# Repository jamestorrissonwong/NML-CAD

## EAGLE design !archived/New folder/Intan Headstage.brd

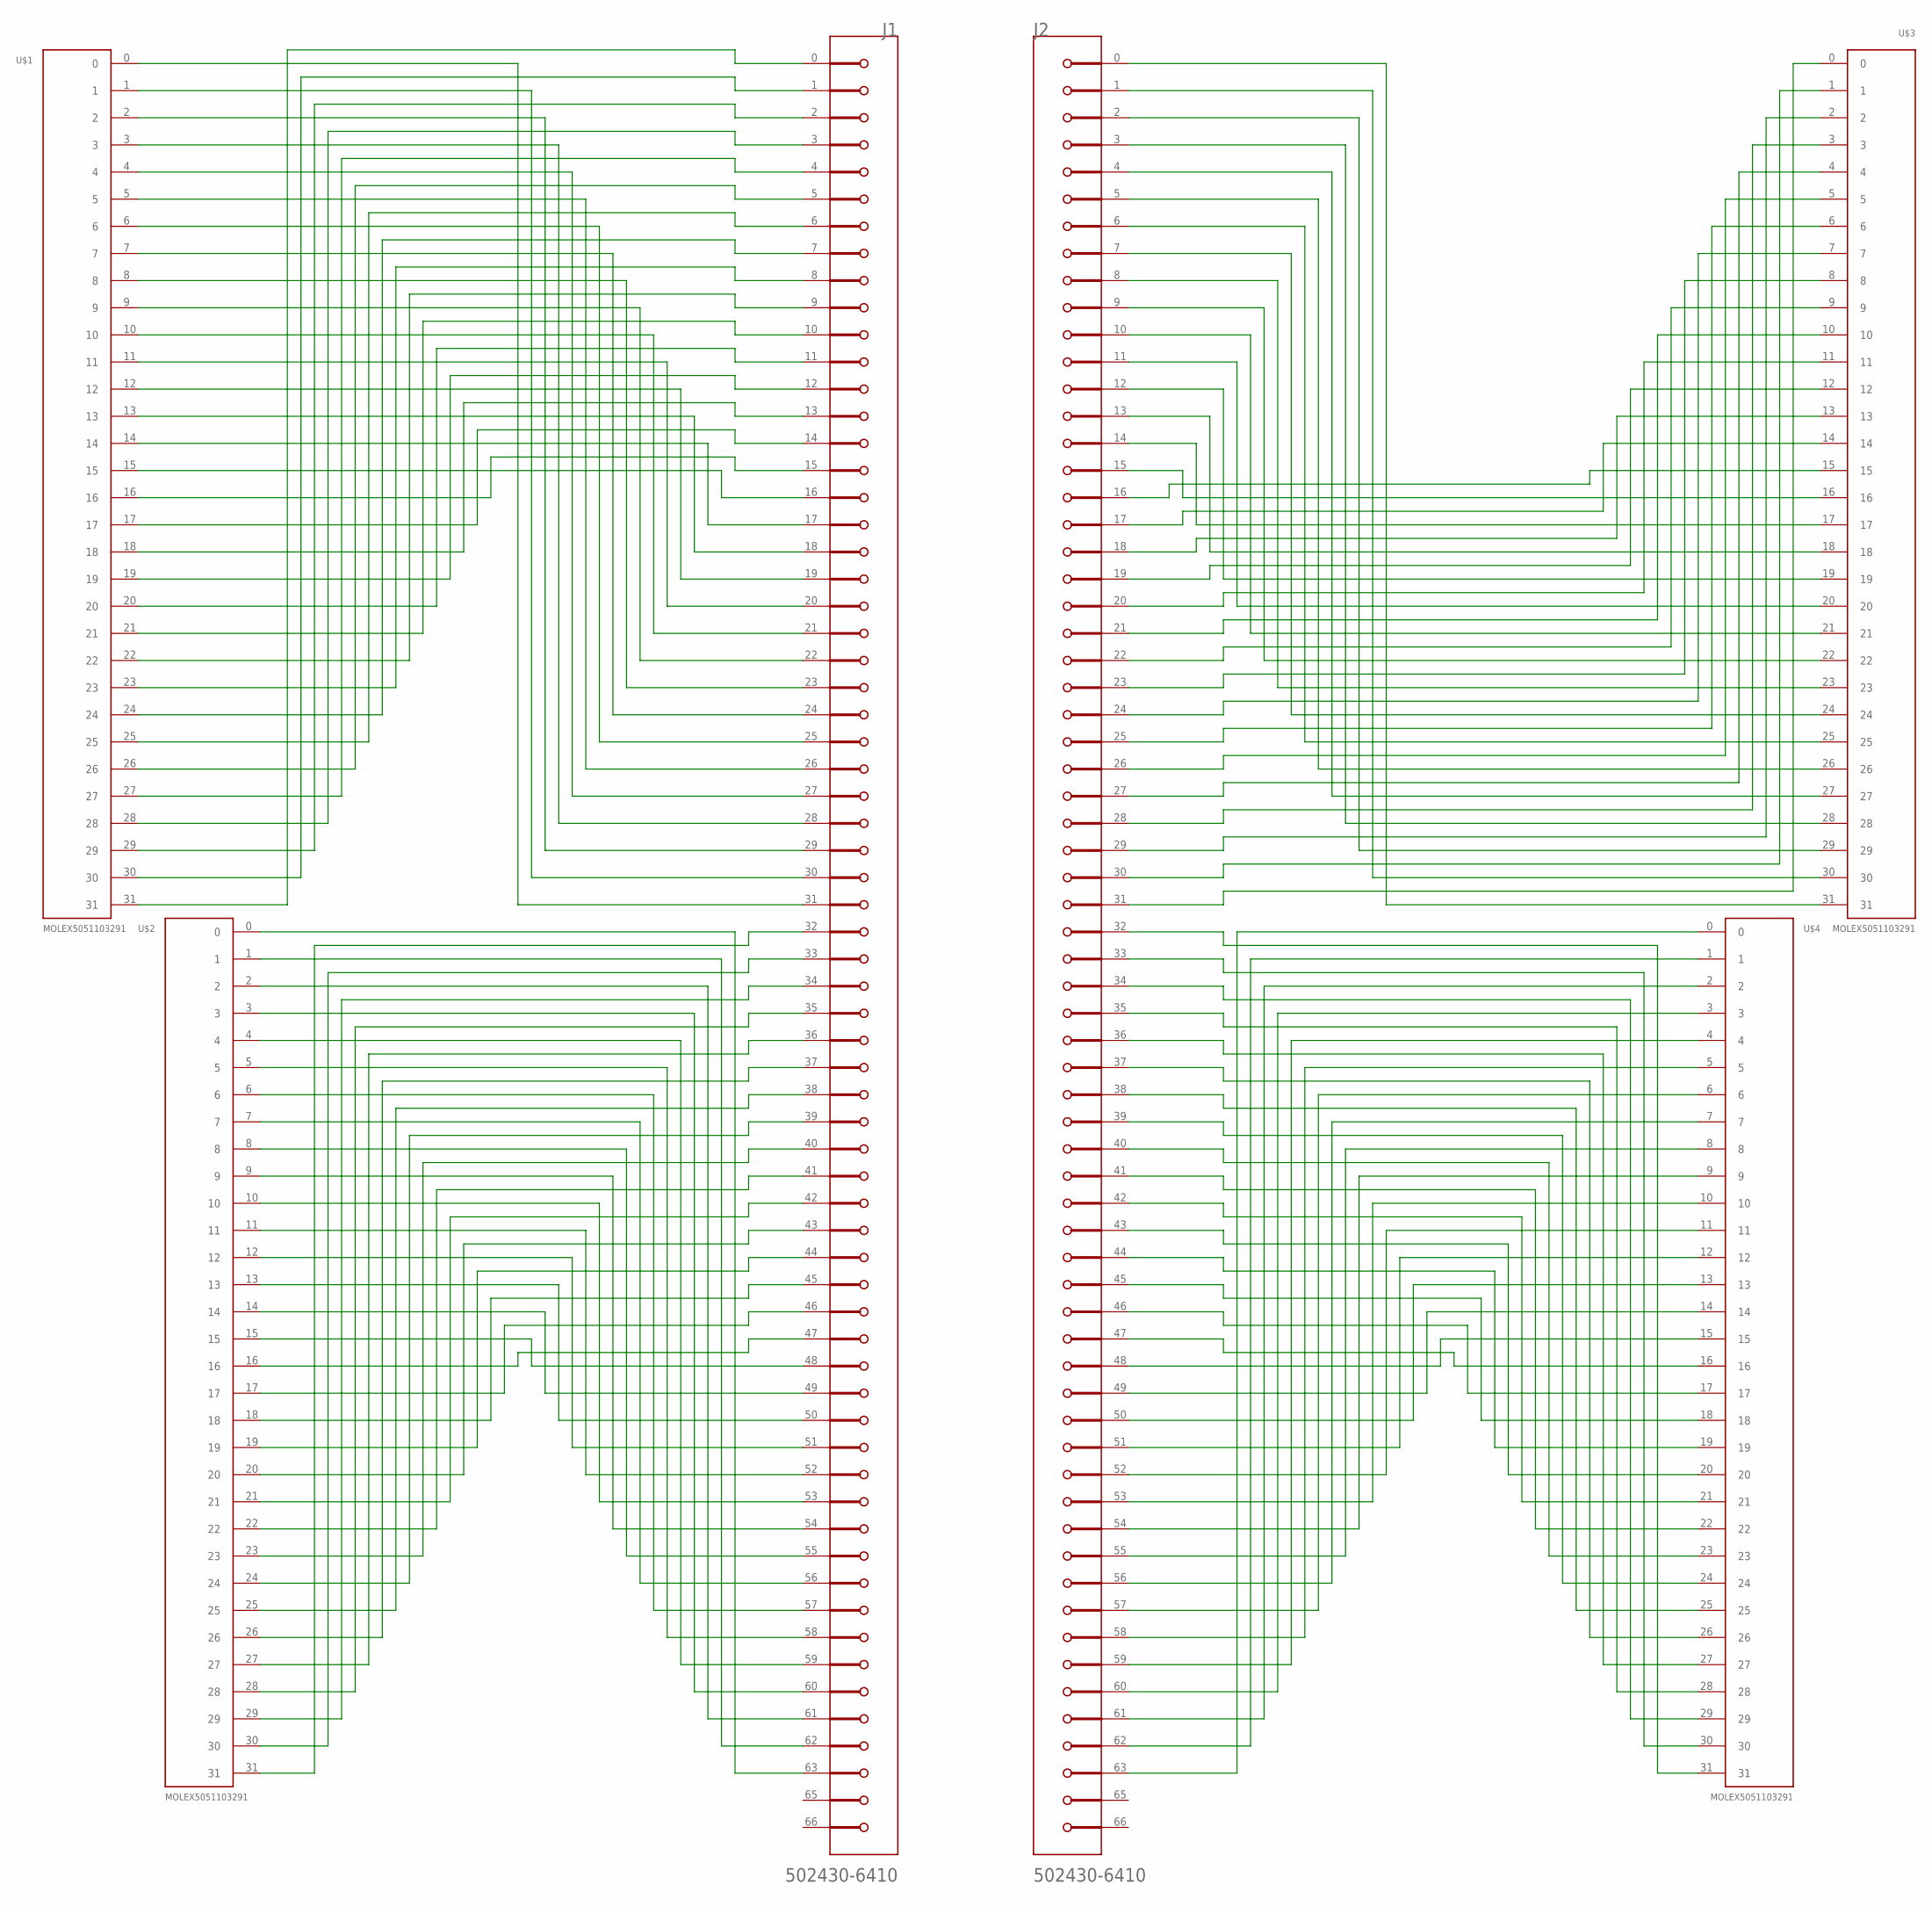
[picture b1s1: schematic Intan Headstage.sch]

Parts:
J1, J2: MOLEX_502430-6410MOLEX_502430-6410_0_0; MOLEX_502430-6410_0
U$1, U$2, U$3, U$4: MOLEX5051103291

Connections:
unnamed: J1.31 (32), U$1.0
unnamed: J1.30 (31), U$1.1
unnamed: J1.29 (30), U$1.2
unnamed: J1.28 (29), U$1.3
unnamed: J1.27 (28), U$1.4
unnamed: J1.26 (27), U$1.5
unnamed: J1.25 (26), U$1.6
unnamed: J1.24 (25), U$1.7
unnamed: J1.23 (24), U$1.8
unnamed: J1.22 (23), U$1.9
unnamed: J1.21 (22), U$1.10
unnamed: J1.20 (21), U$1.11
unnamed: J1.19 (20), U$1.12
unnamed: J1.18 (19), U$1.13
unnamed: J1.17 (18), U$1.14
unnamed: J1.16 (17), U$1.15
unnamed: J1.15 (16), U$1.16
unnamed: J1.14 (15), U$1.17
unnamed: J1.13 (14), U$1.18
unnamed: J1.12 (13), U$1.19
unnamed: J1.11 (12), U$1.20
unnamed: J1.10 (11), U$1.21
unnamed: J1.9 (10), U$1.22
unnamed: J1.8 (9), U$1.23
unnamed: J1.7 (8), U$1.24
unnamed: J1.6 (7), U$1.25
unnamed: J1.5 (6), U$1.26
unnamed: J1.4 (5), U$1.27
unnamed: J1.3 (4), U$1.28
unnamed: J1.2 (3), U$1.29
unnamed: J1.1 (2), U$1.30
unnamed: J1.0 (1), U$1.31
unnamed: J2.0 (1), U$3.31
unnamed: J2.1 (2), U$3.30
unnamed: J2.2 (3), U$3.29
unnamed: J2.3 (4), U$3.28
unnamed: J2.4 (5), U$3.27
unnamed: J2.5 (6), U$3.26
unnamed: J2.6 (7), U$3.25
unnamed: J2.7 (8), U$3.24
unnamed: J2.8 (9), U$3.23
unnamed: J2.9 (10), U$3.22
unnamed: J2.10 (11), U$3.21
unnamed: J2.11 (12), U$3.20
unnamed: J2.12 (13), U$3.19
unnamed: J2.13 (14), U$3.18
unnamed: J2.14 (15), U$3.17
unnamed: J2.15 (16), U$3.16
unnamed: J2.31 (32), U$3.0
unnamed: J2.30 (31), U$3.1
unnamed: J2.29 (30), U$3.2
unnamed: J2.28 (29), U$3.3
unnamed: J2.27 (28), U$3.4
unnamed: J2.26 (27), U$3.5
unnamed: J2.25 (26), U$3.6
unnamed: J2.24 (25), U$3.7
unnamed: J2.23 (24), U$3.8
unnamed: J2.22 (23), U$3.9
unnamed: J2.21 (22), U$3.10
unnamed: J2.20 (21), U$3.11
unnamed: J2.19 (20), U$3.12
unnamed: J2.18 (19), U$3.13
unnamed: J2.17 (18), U$3.14
unnamed: J2.16 (17), U$3.15
unnamed: J1.63 (64), U$2.0
unnamed: J1.62 (63), U$2.1
unnamed: J1.61 (62), U$2.2
unnamed: J1.60 (61), U$2.3
unnamed: J1.59 (60), U$2.4
unnamed: J1.58 (59), U$2.5
unnamed: J1.57 (58), U$2.6
unnamed: J1.56 (57), U$2.7
unnamed: J1.55 (56), U$2.8
unnamed: J1.54 (55), U$2.9
unnamed: J1.53 (54), U$2.10
unnamed: J1.52 (53), U$2.11
unnamed: J1.51 (52), U$2.12
unnamed: J1.50 (51), U$2.13
unnamed: J1.49 (50), U$2.14
unnamed: J1.48 (49), U$2.15
unnamed: J1.47 (48), U$2.16
unnamed: J1.46 (47), U$2.17
unnamed: J1.45 (46), U$2.18
unnamed: J1.44 (45), U$2.19
unnamed: J1.43 (44), U$2.20
unnamed: J1.42 (43), U$2.21
unnamed: J1.41 (42), U$2.22
unnamed: J1.40 (41), U$2.23
unnamed: J1.39 (40), U$2.24
unnamed: J1.38 (39), U$2.25
unnamed: J1.37 (38), U$2.26
unnamed: J1.36 (37), U$2.27
unnamed: J1.35 (36), U$2.28
unnamed: J1.34 (35), U$2.29
unnamed: J1.33 (34), U$2.30
unnamed: J1.32 (33), U$2.31
unnamed: J2.32 (33), U$4.31
unnamed: J2.33 (34), U$4.30
unnamed: J2.34 (35), U$4.29
unnamed: J2.35 (36), U$4.28
unnamed: J2.36 (37), U$4.27
unnamed: J2.37 (38), U$4.26
unnamed: J2.38 (39), U$4.25
unnamed: J2.39 (40), U$4.24
unnamed: J2.40 (41), U$4.23
unnamed: J2.41 (42), U$4.22
unnamed: J2.42 (43), U$4.21
unnamed: J2.43 (44), U$4.20
unnamed: J2.44 (45), U$4.19
unnamed: J2.45 (46), U$4.18
unnamed: J2.46 (47), U$4.17
unnamed: J2.47 (48), U$4.16
unnamed: J2.48 (49), U$4.15
unnamed: J2.49 (50), U$4.14
unnamed: J2.50 (51), U$4.13
unnamed: J2.51 (52), U$4.12
unnamed: J2.52 (53), U$4.11
unnamed: J2.53 (54), U$4.10
unnamed: J2.54 (55), U$4.9
unnamed: J2.55 (56), U$4.8
unnamed: J2.56 (57), U$4.7
unnamed: J2.57 (58), U$4.6
unnamed: J2.58 (59), U$4.5
unnamed: J2.59 (60), U$4.4
unnamed: J2.60 (61), U$4.3
unnamed: J2.61 (62), U$4.2
unnamed: J2.62 (63), U$4.1
unnamed: J2.63 (64), U$4.0

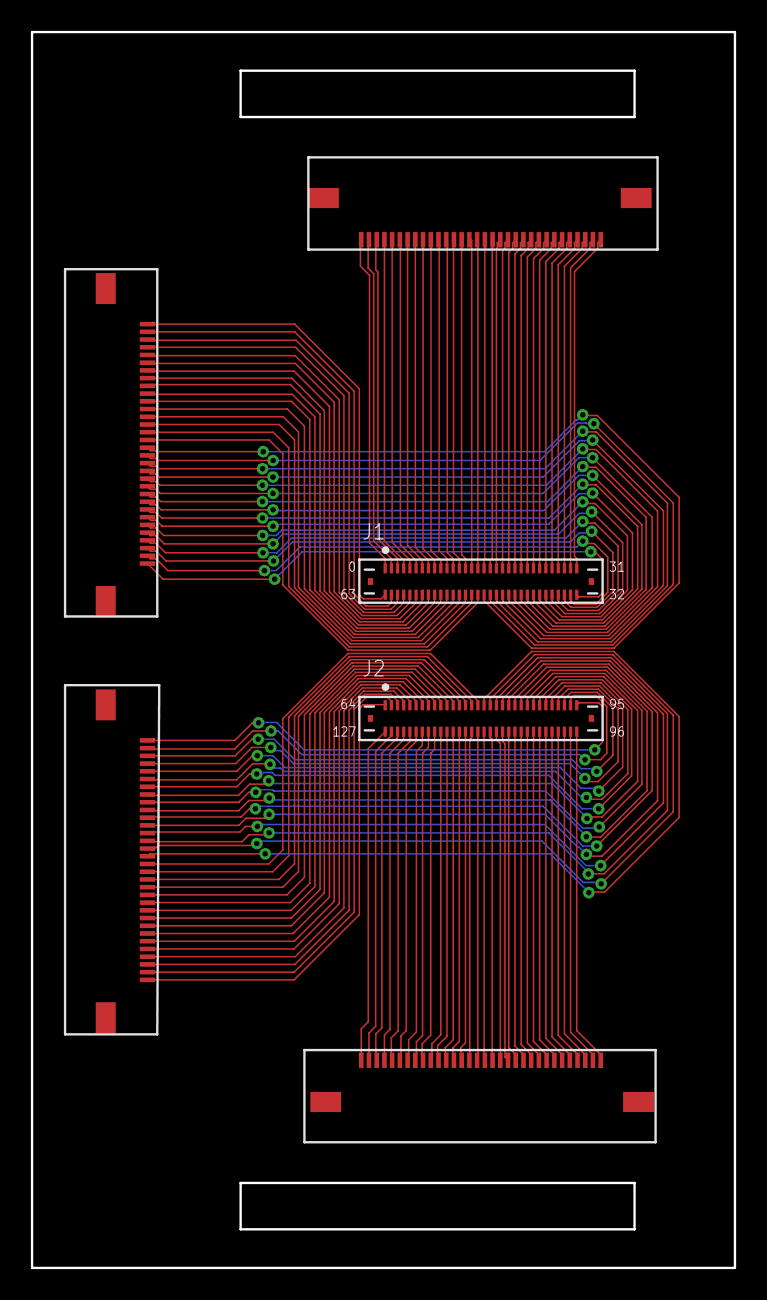
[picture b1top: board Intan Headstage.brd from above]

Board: 2 copper layers, 45.5 x 80.0 mm, 6 parts (0 on the bottom side), 128 nets.

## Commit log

2021-07-27 7/27
2021-08-02 8/2/21
2021-08-03 8/3/21
2021-08-03 8/3/21 v2
2021-08-06 8/6/21
2021-08-28 8/28/21
2021-12-15 XPS 12/15
2021-12-19 121821
2021-12-19 max manip mods
2021-12-23 DT 12-23
2022-01-06 DT 1/5/22
2022-02-23 2/6/22 -- before icts rail updates + 2/22/22 ICTS
2022-06-04 2022-06-04
2022-06-11 2022-06-11
2022-08-11 08/10/22
